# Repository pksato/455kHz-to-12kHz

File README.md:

# IF down converter, 455kHz to 12kHz.
This converter allow a shortwave radio to decode DRM (Digital Radio Mondiale) broadcast using a SDR software.  
  
The circuit use a LA1186N or TA7358AP as mixer, and a analog television chrominance crystal as source to local oscillator.  
The crystal frequency are divide by IC301, and need to selected between 74HC4017 or 74HC4040, depending on choosen crystal frequency.  
To get 12kHz output use 4.433619MHz (PAL) crystal and 74HC4017.  
Using the 74HC4040 and 3.579545MHz (NTSC) or 3.575611MHz (PAL-M) crystal, the output frequency are centered near 8kHz.  
The input impedance of converter are great that 6k.  
Total gain is 12dB.  
  
On the radio, FI signal need to tapped after last IF stage of after 455kHz ceramic filter. Use a 47pF (or lowwer) to decouple the signal.  
  
...

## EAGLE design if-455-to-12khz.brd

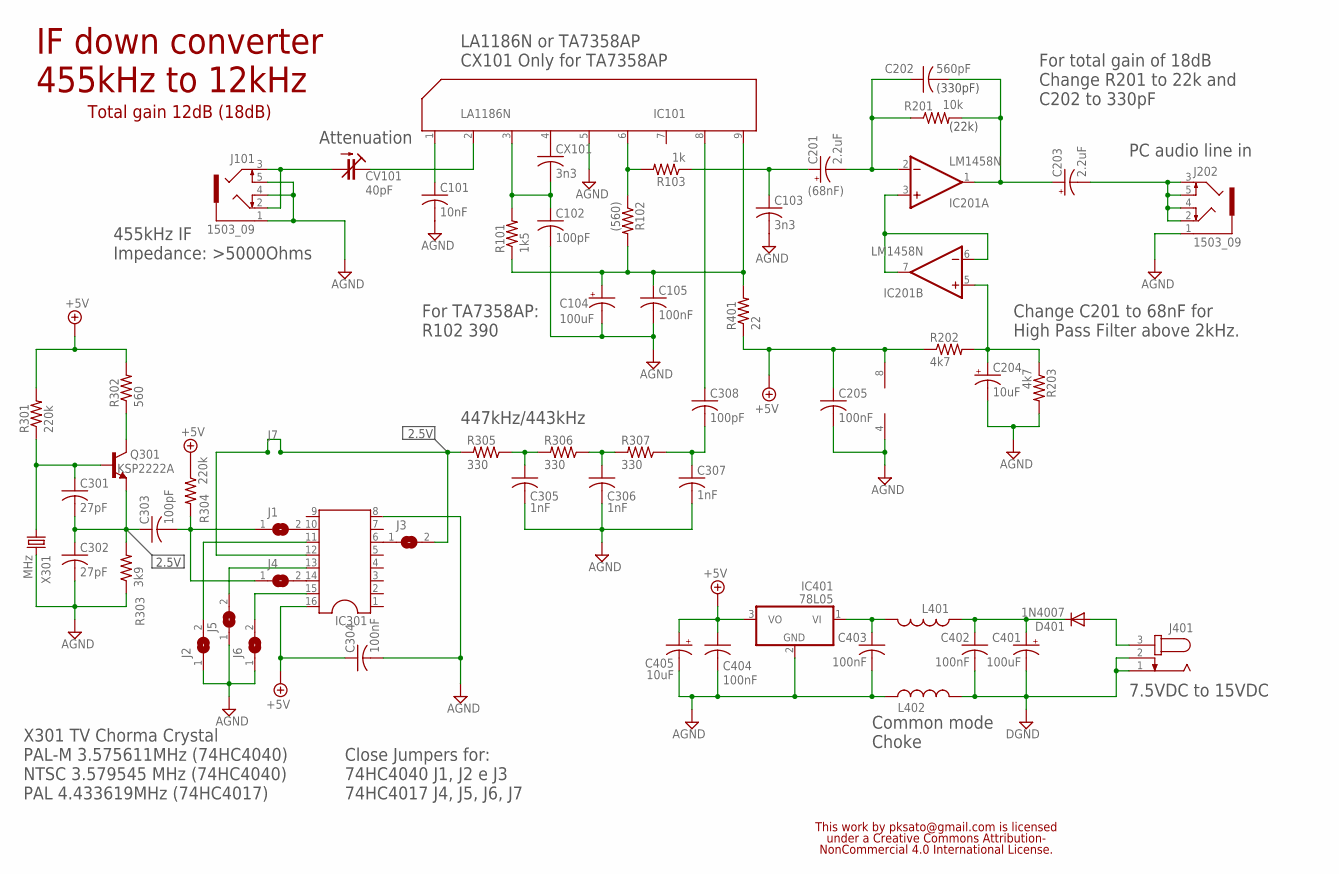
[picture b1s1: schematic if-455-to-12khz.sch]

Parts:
C101: 10nF; C050-025X075
C102, C303, C308: 100pF; C050-025X075
C103: 3n3; C050-025X075
C104, C401: 100uF; E2,5-5
C105, C205, C304, C402, C403, C404: 100nF; C050-025X075
C201: 2.2uF; E5-5
C202: 560pF; C050-025X075
C203: 2.2uF; E2,5-5
C204, C405: 10uF; E2,5-5
C301, C302: 27pF; C050-025X075
C305, C306, C307: 1nF; C050-025X075
CV101: 40pF; CTRIMTZ03
CX101: 3n3; C025-025X050
D401: 1N4007; DO41-10
IC101: LA1186N; SIP09
IC201: LM1458N; DIL08
IC301: DIL16
IC401: 78L05; TO92-
J1, J2, J3, J4, J5, J6: SJ
J101, J202: 1503_09
J401: JACK-PLUG0; SPC4077
L401, L402: L-US0207/10; 0207/10
Q301: KSP2222A; TO92-EBC
R101: 1k5; 0207/10
R102: (560); 0207/10
R103: 1k; 0207/10
R201: 10k; 0207/10
R202, R203: 4k7; 0207/10
R301, R304: 220k; 0207/10
R302: 560; 0207/10
R303: 3k9; 0207/10
R305, R306, R307: 330; 0207/10
R401: 22; 0207/10
X301: MHz; HC49U-LM

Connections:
+5V: C205.1, C304.1, C404.1, C405.+, IC201.8 (V+), IC301.16, IC401.3 (VO), R202.1, R301.2, R302.2, R304.1, R401.1
AGND: C101.2, C102.2, C103.2, C104.-, C105.2, C204.-, C205.2, C302.2, C304.2, C305.2, C306.2, C307.2, C403.2, C404.2, C405.-, IC101.5, IC201.4 (V-), IC301.8, IC401.2 (GND), J2.1, J5.1, J6.1, J101.1, J101.4, J101.5, J202.1, L402.2, R203.2, R303.1, X301.2
DGND: C401.-, C402.2, J401.1, J401.2, L402.1
unnamed: C301.1, Q301.B, R301.1, X301.1
unnamed: C301.2, C302.1, C303.1, Q301.E, R303.2
unnamed: CV101.2 (A), J101.2, J101.3
unnamed: C101.1, IC101.1
unnamed: IC301.12, J3.2, R305.2
unnamed: C104.+, C105.1, IC101.9, R101.1, R102.2, R401.2
unnamed: C303.2, J1.1, J4.1, R304.2
unnamed: C305.1, R305.1, R306.2
unnamed: C306.1, R306.1, R307.2
unnamed: C102.1, CX101.2, IC101.3, R101.2
unnamed: CV101.1 (E), IC101.2
unnamed: C308.1, IC101.8
unnamed: C307.1, C308.2, R307.1
unnamed: IC101.6, R102.1, R103.2
unnamed: C103.1, C201.+, R103.1
unnamed: C403.1, IC401.1 (VI), L401.1
unnamed: C202.2, C203.+, IC201.1 (OUT), R201.2
unnamed: C201.-, C202.1, IC201.2 (-IN), R201.1
unnamed: IC201.3 (+IN), IC201.6 (-IN), IC201.7 (OUT)
unnamed: C203.-, J202.2, J202.3, J202.4, J202.5
unnamed: CX101.1, IC101.4
unnamed: Q301.C, R302.1
unnamed: IC301.14, J4.2
unnamed: IC301.10, J1.2
unnamed: IC301.11, J2.2
unnamed: IC301.15, J6.2
unnamed: IC301.13, J5.2
unnamed: D401.A, J401.3
unnamed: IC301.6, J3.1
unnamed: C401.+, C402.1, D401.C, L401.2
unnamed: C204.+, IC201.5 (+IN), R202.2, R203.1

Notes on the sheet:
LA1186N or TA7358AP CX101 Only for TA7358AP
X301 TV Chorma Crystal PAL-M 3.575611MHz (74HC4040) NTSC 3.579545 MHz (74HC4040) PAL 4.433619MHz (74HC4017)
455kHz IF Impedance: >5000Ohms
PC audio line in
447kHz/443kHz
Close Jumpers for: 74HC4040 J1, J2 e J3 74HC4017 J4, J5, J6, J7
For TA7358AP: R102 390
This work by pksato@gmail.com is licensed under a Creative Commons Attribution- NonCommercial 4.0 International License.
Common mode Choke
7.5VDC to 15VDC
Attenuation
IF down converter 455kHz to 12kHz
Total gain 12dB (18dB)
(68nF)
Change C201 to 68nF for High Pass Filter above 2kHz.
(330pF)
(22k)
For total gain of 18dB Change R201 to 22k and C202 to 330pF
2.5V

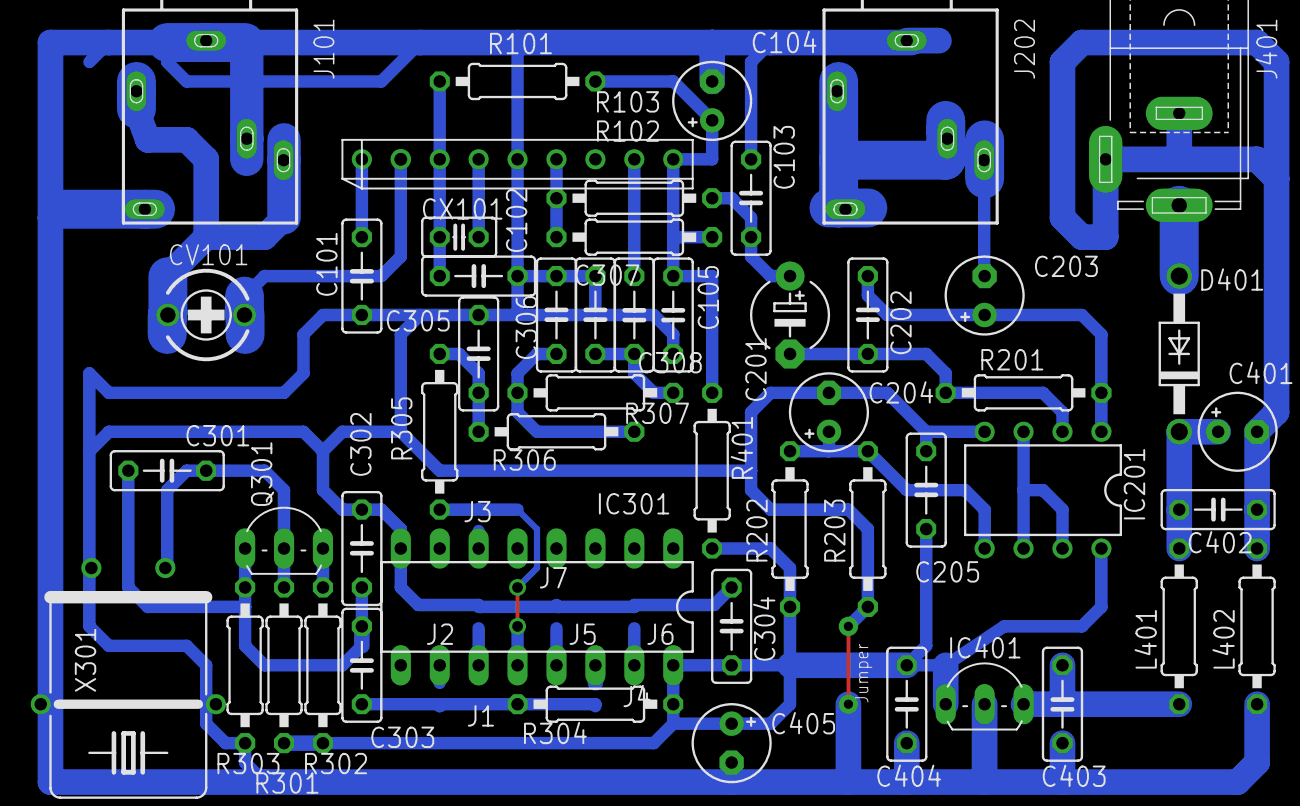
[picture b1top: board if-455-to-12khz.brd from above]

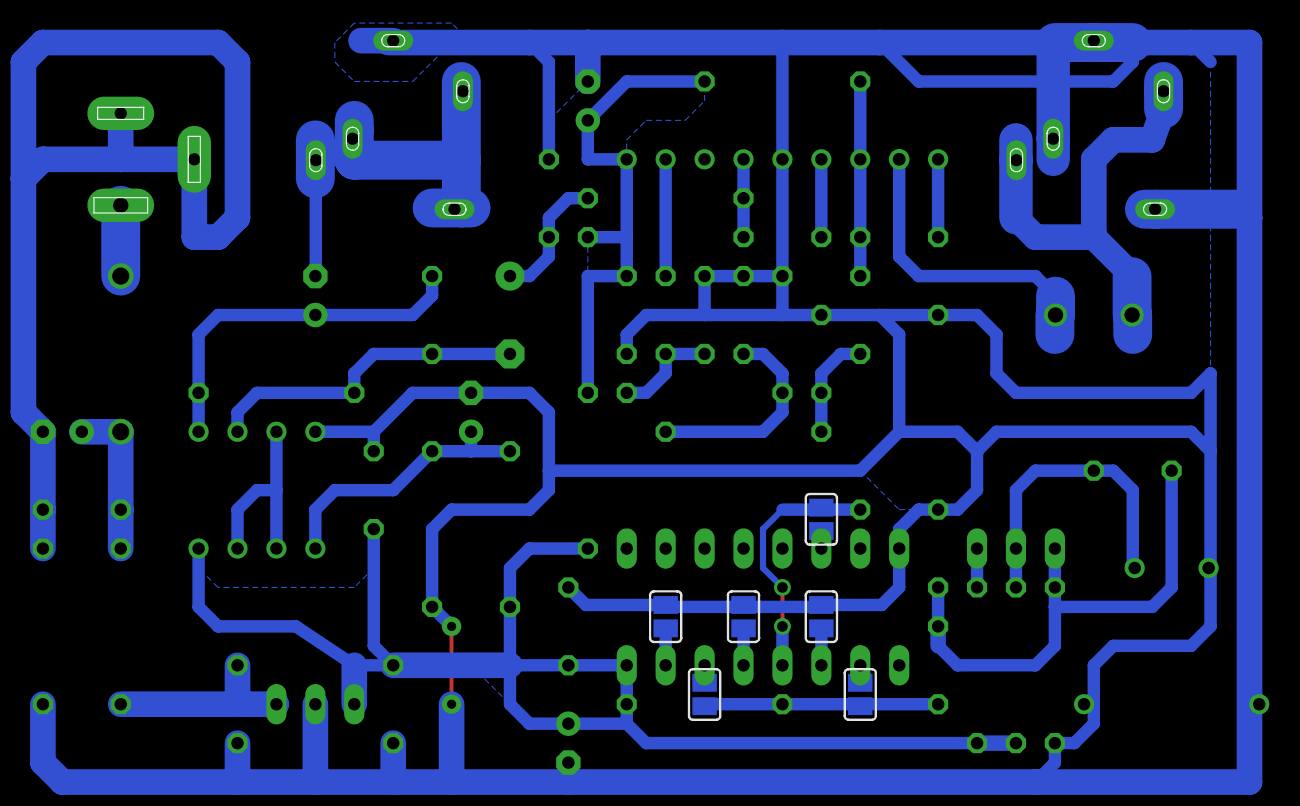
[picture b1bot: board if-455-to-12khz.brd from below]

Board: 2 copper layers, 57 parts (6 on the bottom side), 34 nets.

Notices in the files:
parts and their libraries:
my_parts: This work is licensed under a Creative Commons Attribution-NonCommercial 4.0 International License.
